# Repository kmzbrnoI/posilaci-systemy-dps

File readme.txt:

Tento projekt obsahuje vykresy desek plosnych spoju Posilacich systemu.
FW do procesoru obsahuje repozitar posilaci-systemy-fw.

Vytvoreno v Eagle 7.2.0

Posilaci systemy slouzi pro nabizeni vlaku mezi stanicemi.

(C) Jan Horacek 2010-2015

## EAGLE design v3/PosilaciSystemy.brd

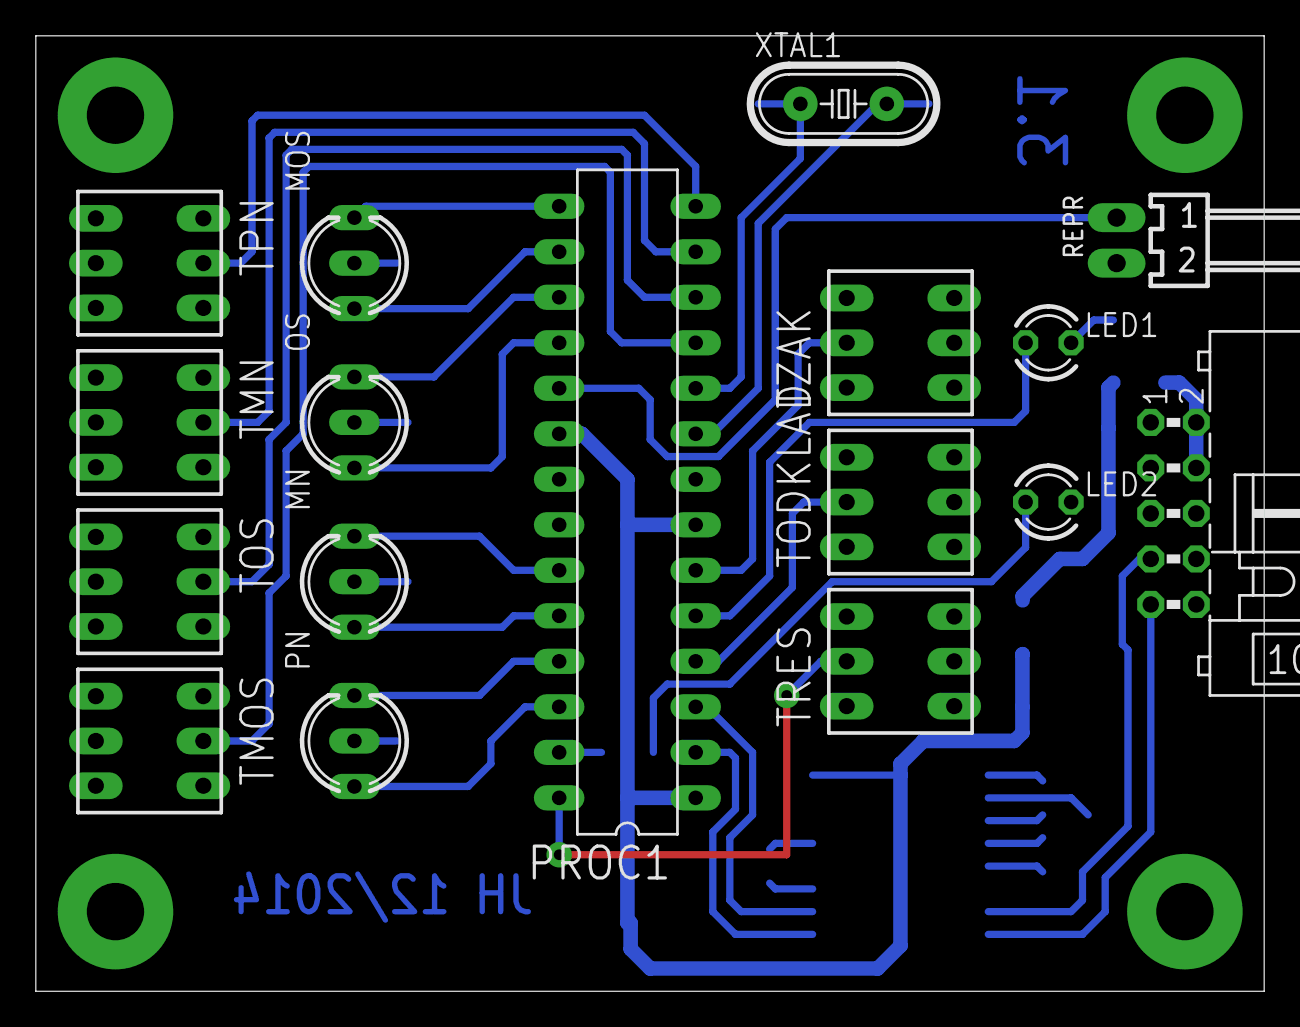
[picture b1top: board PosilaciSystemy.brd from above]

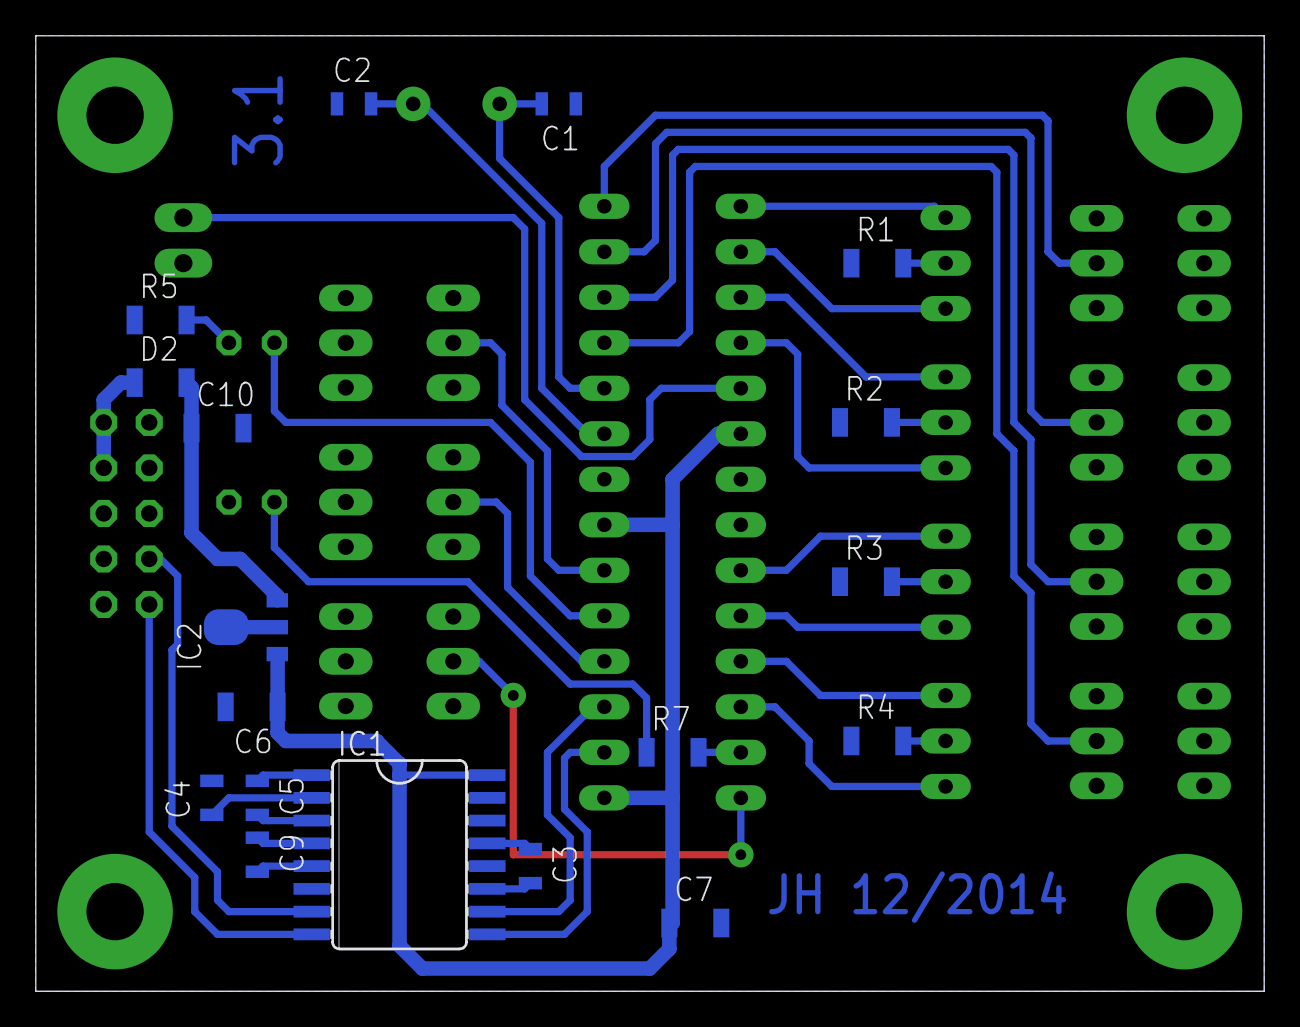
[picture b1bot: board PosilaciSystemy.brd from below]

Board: 2 copper layers, 68.6 x 53.3 mm, 35 parts (18 on the bottom side), 40 nets.

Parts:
C1, C2: 27p; C0805
C3, C4, C5, C9: 1u - 905-185; C0805
C6, C7: 100n; C1206
C10: 10u/25V; C1206
D2: 1N4148-1206; R1206
IC1: MAX232ECWE; SO16L
IC2: 78L05F; SOT89
LED1, LED2: YEL; LED3MM
MN: L-115WEGW; DUOLED-C-5MM
MOS: L-115WEGW; DUOLED-C-5MM
OS: L-115WEGW; DUOLED-C-5MM
PN: L-115WEGW; DUOLED-C-5MM
PROC1: ATMEGA8; DIL28-3
R1, R2, R3, R4, R5, R7: 1k; R1206
REPR: PSH02-02PG; 7395-02
SV1: ML10L
TMN: P-B170H; HORASPINAC
TMOS: P-B170H; HORASPINAC
TODKLAD: P-B170H; HORASPINAC
TOS: P-B170H; HORASPINAC
TPN: P-B170H; HORASPINAC
TRES: P-B170H; HORASPINAC
TZAK: P-B170H; HORASPINAC
XTAL1: 7.3728 MHz; HC49/S

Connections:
232-IN: IC1.8, SV1.9
232-OUT: IC1.7, SV1.7
GND: C1.1, C2.1, C3.2, C4.2, C6.2, C7.2, C10.2, IC1.11, IC1.15, IC2.2, IC2.2@1, LED2.K, PROC1.8, PROC1.22, R1.1, R2.1, R3.1, R4.1, R5.1, REPR.2, SV1.1, SV1.3, TMN.NAPAJENI1, TMOS.NAPAJENI1, TODKLAD.NAPAJENI1, TODKLAD.NAPAJENI2, TODKLAD.ODEPNUTO2, TODKLAD.SEPNUTO2, TOS.NAPAJENI1, TPN.NAPAJENI1, TRES.NAPAJENI1, TRES.NAPAJENI2, TRES.ODEPNUTO2, TRES.SEPNUTO2, TZAK.NAPAJENI1
L3: MN.C, R3.2
L4: PN.C, R4.2
L-ODKLAD: PROC1.27, R7.2
L-ZAK: LED1.A, PROC1.5
LG-MN: MN.AX, PROC1.24
LG-MOS: MOS.AX, PROC1.16
LG-OS: OS.AX, PROC1.18
LG-PN: PN.AX, PROC1.26
LR-MN: MN.AR, PROC1.23
LR-MOS: MOS.AR, PROC1.15
LR-OS: OS.AR, PROC1.17
LR-PN: PN.AR, PROC1.25
unnamed: LED1.K, R5.2
unnamed: LED2.A, R7.1
unnamed: C5.1, IC1.1
unnamed: C5.2, IC1.3
unnamed: C9.1, IC1.4
unnamed: C10.1, D2.K, IC2.3
unnamed: C9.2, IC1.5
unnamed: C3.1, IC1.6, IC1.13
unnamed: C4.1, IC1.2
unnamed: OS.C, R2.2
unnamed: MOS.C, R1.2
REPRACEK: PROC1.19, REPR.1
RXD: IC1.9, PROC1.2
TLC-MN: PROC1.12, TOS.SEPNUTO1
TLC-MOS: PROC1.14, TPN.SEPNUTO1
TLC-ODKLAD: PROC1.4, TODKLAD.SEPNUTO1
TLC-OS: PROC1.13, TMN.SEPNUTO1
TLC-PN: PROC1.11, TMOS.SEPNUTO1
TLC-RESET: PROC1.28, TRES.SEPNUTO1
TLC-ZAK: PROC1.6, TZAK.SEPNUTO1
TXD: IC1.10, PROC1.3
VCC: C6.1, C7.1, IC1.16, IC2.1, PROC1.1, PROC1.7, PROC1.20
VCC/2: D2.A, SV1.2, SV1.4
XTAL1: C2.2, PROC1.9, XTAL1.2
XTAL2: C1.2, PROC1.10, XTAL1.1

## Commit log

2015-05-30 Prvni commit.
2015-05-30 Pridan autor.
2015-05-30 Odstraneno eagle.epf
2015-05-30 Dopsano "Vytvoreno v Eagle 5.6.0"
2016-04-29 Pridan obsah vrsty milingKrab.
    Ulozeno ve formatu Eagle 7.2.0.
2016-04-29 Uprava readme.
